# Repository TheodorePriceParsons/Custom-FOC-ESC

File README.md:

# Custom FOC ESC

A field-oriented-control motor controller designed from scratch: a 4-layer power board, STM32G474 firmware with cascaded current and speed loops, and an automated hardware-in-the-loop test bench that verifies the drive against written requirements.

https://github.com/user-attachments/assets/c9957159-f915-4ab0-a1e7-d9c9039c102c

*First closed-loop FOC spin (Oct 2026); kept for sentimental value.*

## Highlights

- **Hardware:** DRV8305 gate driver, AON7544 MOSFETs, 5 mΩ low-side shunts on all three phases, MT6701 magnetic encoder, 4-layer stackup with dedicated ground and power planes.
- **Firmware:** sensored FOC at 10.4 kHz on the STM32G474's high-resolution timer, min/max SVPWM, PI current loops with conditional-integration anti-windup, and an outer speed loop. Worst-case ISR load is 37 to 46 % of the cycle budget.
- **Verification:** one command runs every test on the hardware, identifies the motor (R, L, Kt, J), predicts each result from those parameters, and reports predicted vs measured with pass/fail per requirement.
- **Safety:** host watchdog in the control ISR, latched E-stop, overcurrent and gate-driver fault trips.

## Test results

<!-- bench:start -->
Results are published here from the test bench with `python bench/publish.py <run folder>`.
<!-- bench:end -->

## How it works

```
 NUCLEO-G474RE                                        ESC board                    GM4108H motor
 ┌──────────────────────────────────────────┐        ┌─────────────────────┐
 │ HRTIM ── 3 x PWM (center-aligned) ───────┼──────▶ │ DRV8305 → 3 half-   │ ───▶ phases A/B/C
 │   └─ ADC trigger at PWM center           │        │ bridges (AON7544)   │
 │ ADC1 + DMA ◀── 3 shunt amplifiers ───────┼─────── │ 5 mΩ shunts, 40 V/V │
 │ SPI3 (shared bus) ◀──────────────────────┼─────── │ DRV8305 config/stat │
 │                  ◀──────────────────────┼─────── │ MT6701 encoder (SSI)│ ◀── magnet on rotor
 │ foc_isr() @ 10.38 kHz                    │        └─────────────────────┘
 │ LPUART1 ◀──▶ test bench (PC)             │
 └──────────────────────────────────────────┘
```

Each control period:

1. The HRTIM triggers the ADC at the PWM center, when all low-side switches are on and the shunts carry the phase currents.
2. The ISR reads the encoder, converts the mechanical angle to the electrical angle, and transforms the phase currents into the rotor frame (Clarke, then Park), where they are DC.
3. Two PI controllers regulate $i_d$ to 0 and $i_q$ to the torque command. Every 10th tick the speed PI sets the $i_q$ command.
4. The voltage command is transformed back (inverse Park) and turned into three duty cycles with min/max SVPWM, which reaches the full $V_{bus}/\sqrt{3}$ phase voltage.

The derivations, including the PI design by pole-zero cancellation, the speed loop design and the expected step responses, are in [docs/control-math.md](docs/control-math.md).

## Test bench

The bench (in [`bench/`](bench/)) drives the ESC over UART from Python:

```
python bench/run_bench.py --port COM5 --tune-current
```

- The firmware injects each step at an exact control-loop sample and records 2048 samples to RAM; the PC downloads the capture and computes every metric from it.
- It measures R and L from a d-axis voltage step, computes current-loop gains for 300 Hz bandwidth, then verifies the loop it just tuned.
- Each result is predicted from the parameters measured in the same run, so the report checks the design math as well as the hardware.
- Requirements have IDs and limits in [`bench/spec.py`](bench/spec.py); each test runs N times and reports mean ± std.
- The host software is checked against a plant simulator with the same protocol (`--sim`), and the metric code has unit tests.

Details: [bench/README.md](bench/README.md), wire protocol: [bench/PROTOCOL.md](bench/PROTOCOL.md).

## Hardware

| | |
|---|---|
| Gate driver | TI DRV8305, 3-PWM mode, SPI configuration, integrated current-sense amplifiers (40 V/V) |
| Power stage | AON7544 N-channel MOSFETs, 3 half-bridges |
| Current sensing | 5 mΩ low-side shunts on all three phases (±8 A sense range), sampled at PWM center |
| Position | MT6701 14-bit magnetic encoder over SSI, sharing one SPI bus with the DRV8305 |
| Stackup | 4 layers: power stage, solid ground, PVDD plane, signals |
| Power | 3S LiPo (12 V), XT60; 2 mm bullet connectors for swappable motor leads |
| Controller | NUCLEO-G474RE (Cortex-M4F, 170 MHz) |
| Motor | GM4108H-120T gimbal motor, 11 pole pairs |

KiCad projects are in `hardware/` and motor mounts in `mechanical/`.

## Bring-up notes

Four wiring and configuration mistakes took most of the bring-up time:

1. The board ground was on the bench supply's earth terminal, so PVDD was never powered. The Nucleo back-fed 3.3 V into the DRV8305's regulator pin, which made PWRGD look healthy while SPI read all zeros.
2. The nFAULT jumper was on the wrong Nucleo pin, so the MCU read a floating input.
3. PWM went to the INL inputs; in 3-PWM mode the DRV8305 ignores INL, so every low-side gate sat on.
4. One ADC pin on the Nucleo gave a large drifting offset. Swapping channels proved the board signal was clean, and moving phase C to another pin fixed it.

## Repository

| Folder | Contents |
|---|---|
| `firmware/` | STM32CubeIDE project. Control code in `App/foc/`, drivers in `App/drivers/`, bench interface in `App/bench/` |
| `hardware/` | KiCad projects for each board revision |
| `mechanical/` | Motor and encoder mounts (STEP) |
| `bench/` | Automated test bench, requirements, reports |
| `docs/` | Control math and figures |

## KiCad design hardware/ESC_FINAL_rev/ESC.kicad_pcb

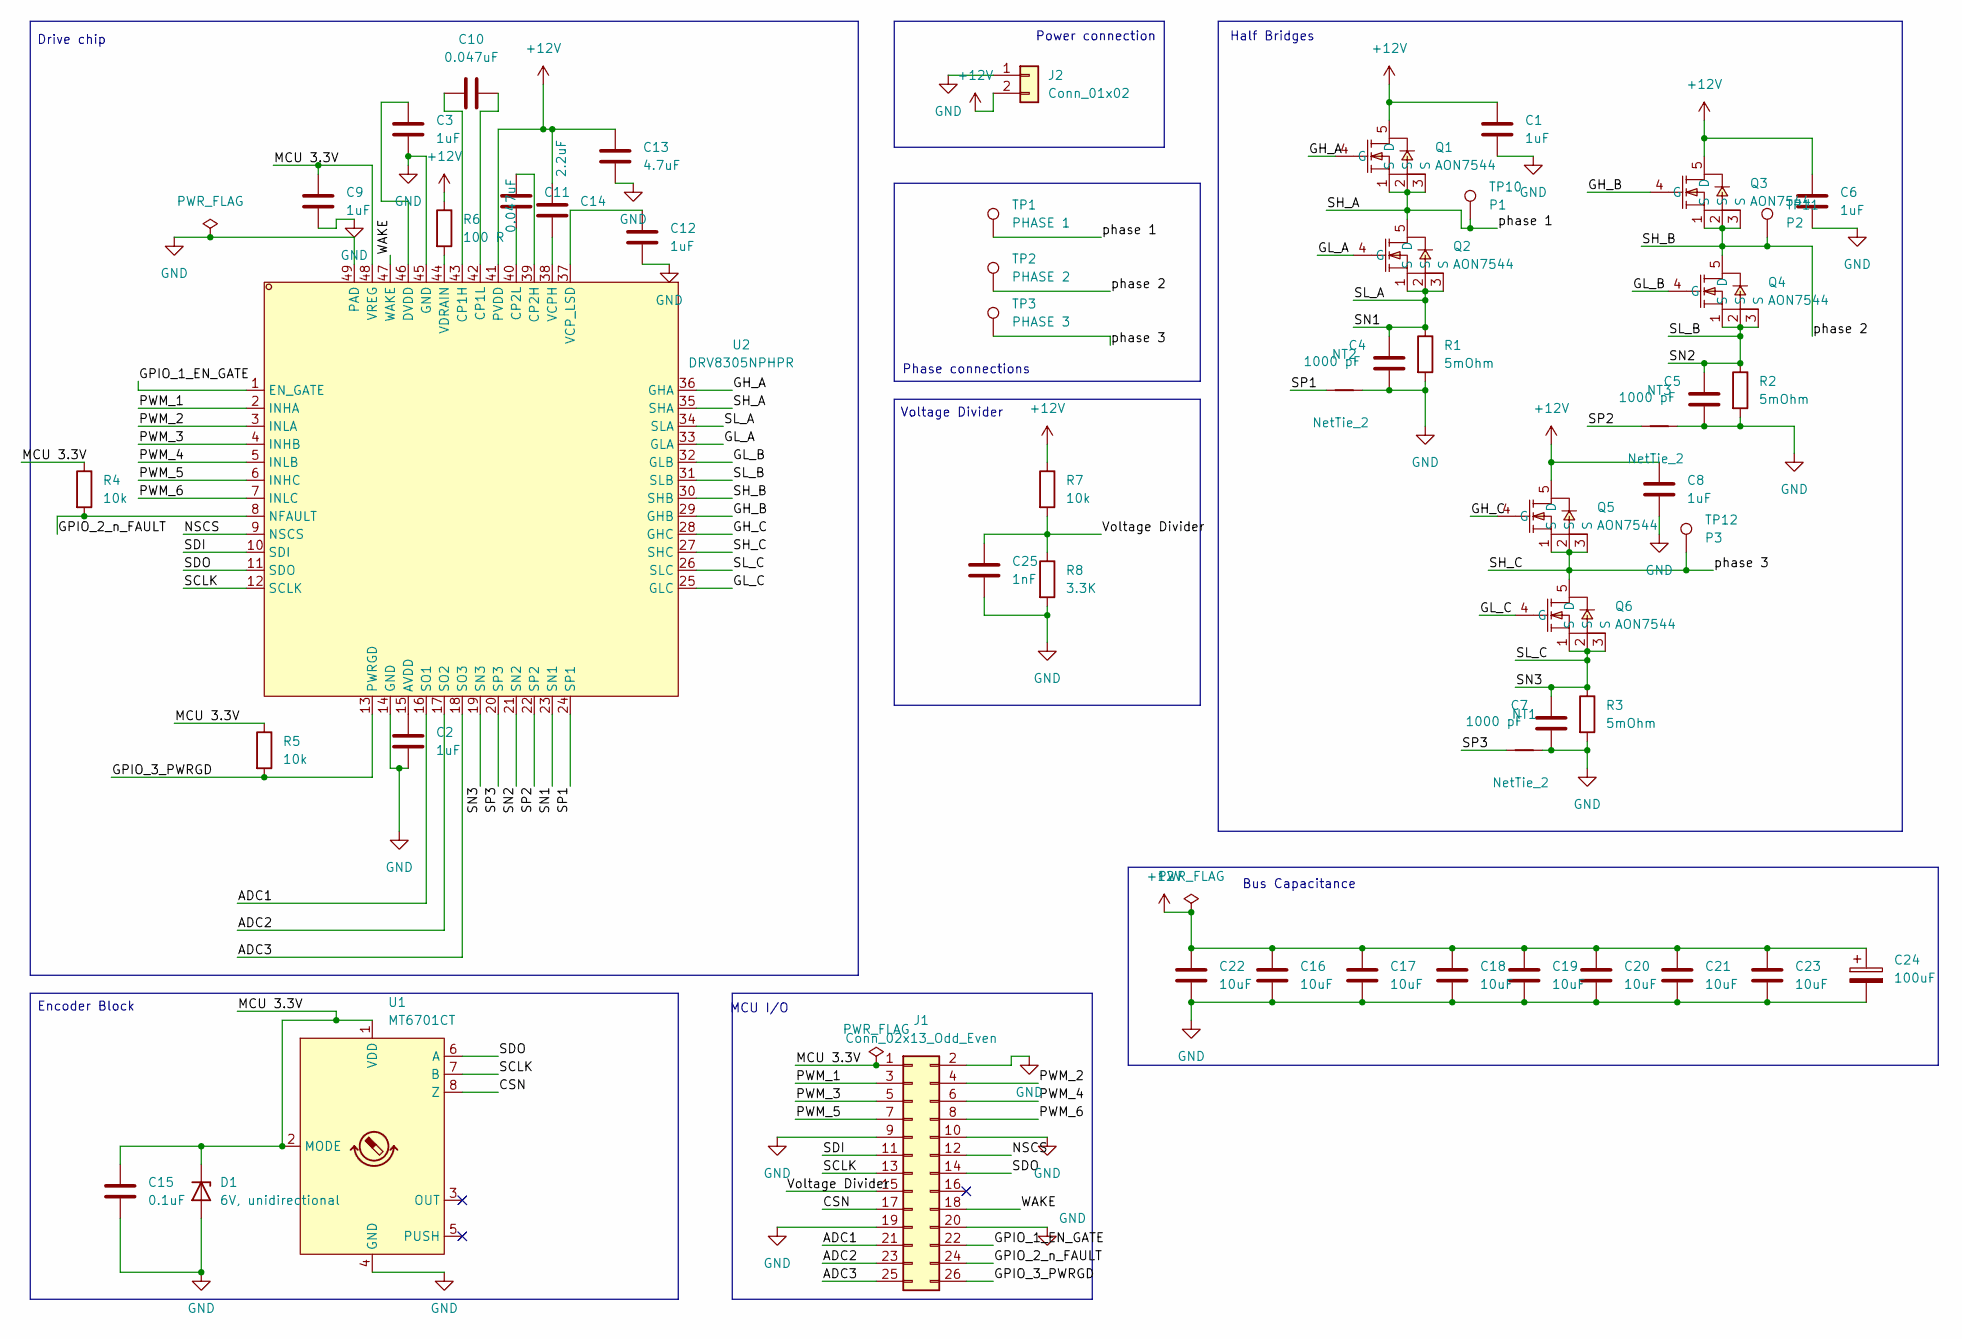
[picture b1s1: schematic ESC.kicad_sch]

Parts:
C1, C2, C3, C6, C8, C9, C12: 1uF; C_0603_1608Metric; LCSC ID C29936
C4, C5, C7: 1000 pF; C_0603_1608Metric; LCSC ID C1588
C10, C11: 0.047uF; C_0603_1608Metric; LCSC ID C1622
C13: 4.7uF; C_0805_2012Metric; LCSC ID C1779
C14: 2.2uF; C_0805_2012Metric; LCSC ID C49217
C15: 0.1uF; C_0603_1608Metric; LCSC ID C14663
C16, C17, C18, C19, C20, C21, C22, C23: 10uF; C_1206_3216Metric; LCSC ID C89632
C24: 100uF; CP_Elec_6.3x5.9; LCSC ID C46550460
C25: 1nF; C_0402_1005Metric; LCSC ID C53547
D1: 6V, unidirectional; D_SOD-323; LCSC ID C7461
J1: Conn_02x13_Odd_Even; PinHeader_2x13_P2.54mm_Vertical
J2: Conn_01x02; AMASS_XT60-F_1x02_P7.20mm_Vertical
NT1, NT2, NT3: NetTie_2; NetTie-2_SMD_Pad0.5mm
Q1, Q2, Q3, Q4, Q5, Q6: AON7544; DFN-8_L3.3-W3.3-P0.65-BL-2; MPN AON7544; LCSC ID C315567
R1, R2, R3: 5mOhm; R_2512_6332Metric; LCSC ID C500739
R4, R5: 10k; R_0402_1005Metric; LCSC ID C25744
R6: 100 R; R_0603_1608Metric; LCSC ID C22775
R7: 10k; R_0402_1005Metric; LCSC ID C2889342
R8: 3.3K; R_0402_1005Metric; LCSC ID C2889356
TP1: PHASE 1; TestPoint_THTPad_2.0x2.0mm_Drill1.0mm
TP2: PHASE 2; TestPoint_THTPad_2.0x2.0mm_Drill1.0mm
TP3: PHASE 3; TestPoint_THTPad_2.0x2.0mm_Drill1.0mm
TP10: P1; TestPoint_THTPad_D2.0mm_Drill1.0mm
TP11: P2; TestPoint_THTPad_D2.0mm_Drill1.0mm
TP12: P3; TestPoint_THTPad_D2.0mm_Drill1.0mm
U1: MT6701CT; SO-8_3.9x4.9mm_P1.27mm; LCSC ID C2856764
U2: DRV8305NPHPR; HTQFP-48_L7.0-W7.0-P0.50-LS9.0-BL-EP5.1; MPN DRV8305NPHPR; LCSC ID C75602

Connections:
+12V: C1.1, C6.1, C8.1, C13.1, C14.1, C16.1, C17.1, C18.1, C19.1, C20.1, C21.1, C22.1, C23.1, C24.1, J2.2, Q1.5 (D), Q3.5 (D), Q5.5 (D), R6.1, R7.1, U2.41 (PVDD)
/ADC1: J1.21, U2.16 (SO1)
/ADC2: J1.23, U2.17 (SO2)
/ADC3: J1.25, U2.18 (SO3)
/CSN: J1.17, U1.8 (Z)
/GH_A: Q1.4 (G), U2.36 (GHA)
/GH_B: Q3.4 (G), U2.29 (GHB)
/GH_C: Q5.4 (G), U2.28 (GHC)
/GL_A: Q2.4 (G), U2.33 (GLA)
/GL_B: Q4.4 (G), U2.32 (GLB)
/GL_C: Q6.4 (G), U2.25 (GLC)
/GPIO_1_EN_GATE: J1.22, U2.1 (EN_GATE)
/GPIO_2_n_FAULT: J1.24, R4.2, U2.8 (NFAULT)
/GPIO_3_PWRGD: J1.26, R5.2, U2.13 (PWRGD)
/MCU 3.3V: C9.1, C15.1, D1.1 (K), J1.1, R4.1, R5.1, U1.1 (VDD), U1.2 (MODE), U2.48 (VREG)
/NSCS: J1.12, U2.9 (NSCS)
/PWM_1: J1.3, U2.2 (INHA)
/PWM_2: J1.4, U2.3 (INLA)
/PWM_3: J1.5, U2.4 (INHB)
/PWM_4: J1.6, U2.5 (INLB)
/PWM_5: J1.7, U2.6 (INHC)
/PWM_6: J1.8, U2.7 (INLC)
/SCLK: J1.13, U1.7 (B), U2.12 (SCLK)
/SDI: J1.11, U2.10 (SDI)
/SDO: J1.14, U1.6 (A), U2.11 (SDO)
/SH_A: Q1.1 (S), Q1.2 (S), Q1.3 (S), Q2.5 (D), TP1.1 (1_1), TP10.1 (1_1), U2.35 (SHA)
/SH_B: Q3.1 (S), Q3.2 (S), Q3.3 (S), Q4.5 (D), TP2.1 (1_1), TP11.1 (1_1), U2.30 (SHB)
/SH_C: Q5.1 (S), Q5.2 (S), Q5.3 (S), Q6.5 (D), TP3.1 (1_1), TP12.1 (1_1), U2.27 (SHC)
/SL_A: C4.1, Q2.1 (S), Q2.2 (S), Q2.3 (S), R1.1, U2.23 (SN1), U2.34 (SLA)
/SL_B: C5.1, Q4.1 (S), Q4.2 (S), Q4.3 (S), R2.1, U2.21 (SN2), U2.31 (SLB)
/SL_C: C7.1, Q6.1 (S), Q6.2 (S), Q6.3 (S), R3.1, U2.19 (SN3), U2.26 (SLC)
/SP1: NT2.1, U2.24 (SP1)
/SP2: NT3.1, U2.22 (SP2)
/SP3: NT1.1, U2.20 (SP3)
/Voltage Divider: C25.1, J1.15, R7.2, R8.1
/WAKE: J1.18, U2.47 (WAKE)
GND: C1.2, C2.2, C3.2, C4.2, C5.2, C6.2, C7.2, C8.2, C9.2, C12.2, C13.2, C15.2, C16.2, C17.2, C18.2, C19.2, C20.2, C21.2, C22.2, C23.2, C24.2, C25.2, D1.2 (A), J1.2, J1.9, J1.10, J1.19, J1.20, J2.1, NT1.2, NT2.2, NT3.2, R1.2, R2.2, R3.2, R8.2, U1.4 (GND), U2.14 (GND), U2.45 (GND), U2.49 (PAD)
unnamed: C2.1, U2.15 (AVDD)
unnamed: C10.1, U2.43 (CP1H)
unnamed: C10.2, U2.42 (CP1L)
unnamed: C11.2, U2.39 (CP2H)
unnamed: C11.1, U2.40 (CP2L)
unnamed: C3.1, U2.46 (DVDD)
unnamed: C14.2, U2.38 (VCPH)
unnamed: C12.1, U2.37 (VCP_LSD)
unnamed: R6.2, U2.44 (VDRAIN)

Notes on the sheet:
Voltage Divider
MCU I/O
Phase connections
Encoder Block
Bus Capacitance
Drive chip
Half Bridges
Power connection

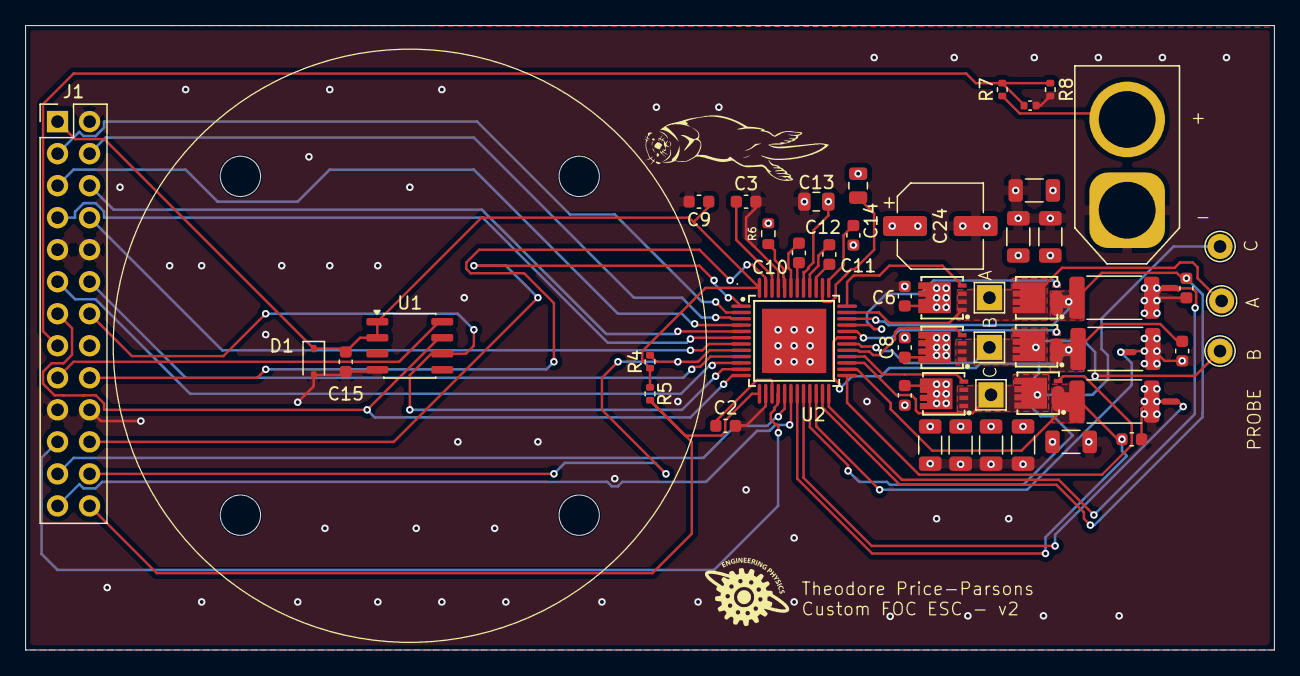
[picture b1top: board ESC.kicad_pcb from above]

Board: 4 copper layers, 99.1 x 49.5 mm, 53 parts (0 on the bottom side), 46 nets.
